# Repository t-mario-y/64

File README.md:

# 64

Splitted, Cherry MX switch, 64 keys, ortholinear mechanical keyboard.

MCU: [Waveshare RP2040-zero](https://www.waveshare.com/wiki/RP2040-Zero)  
Firmware: [KMK firmware](https://github.com/KMKfw/kmk_firmware)

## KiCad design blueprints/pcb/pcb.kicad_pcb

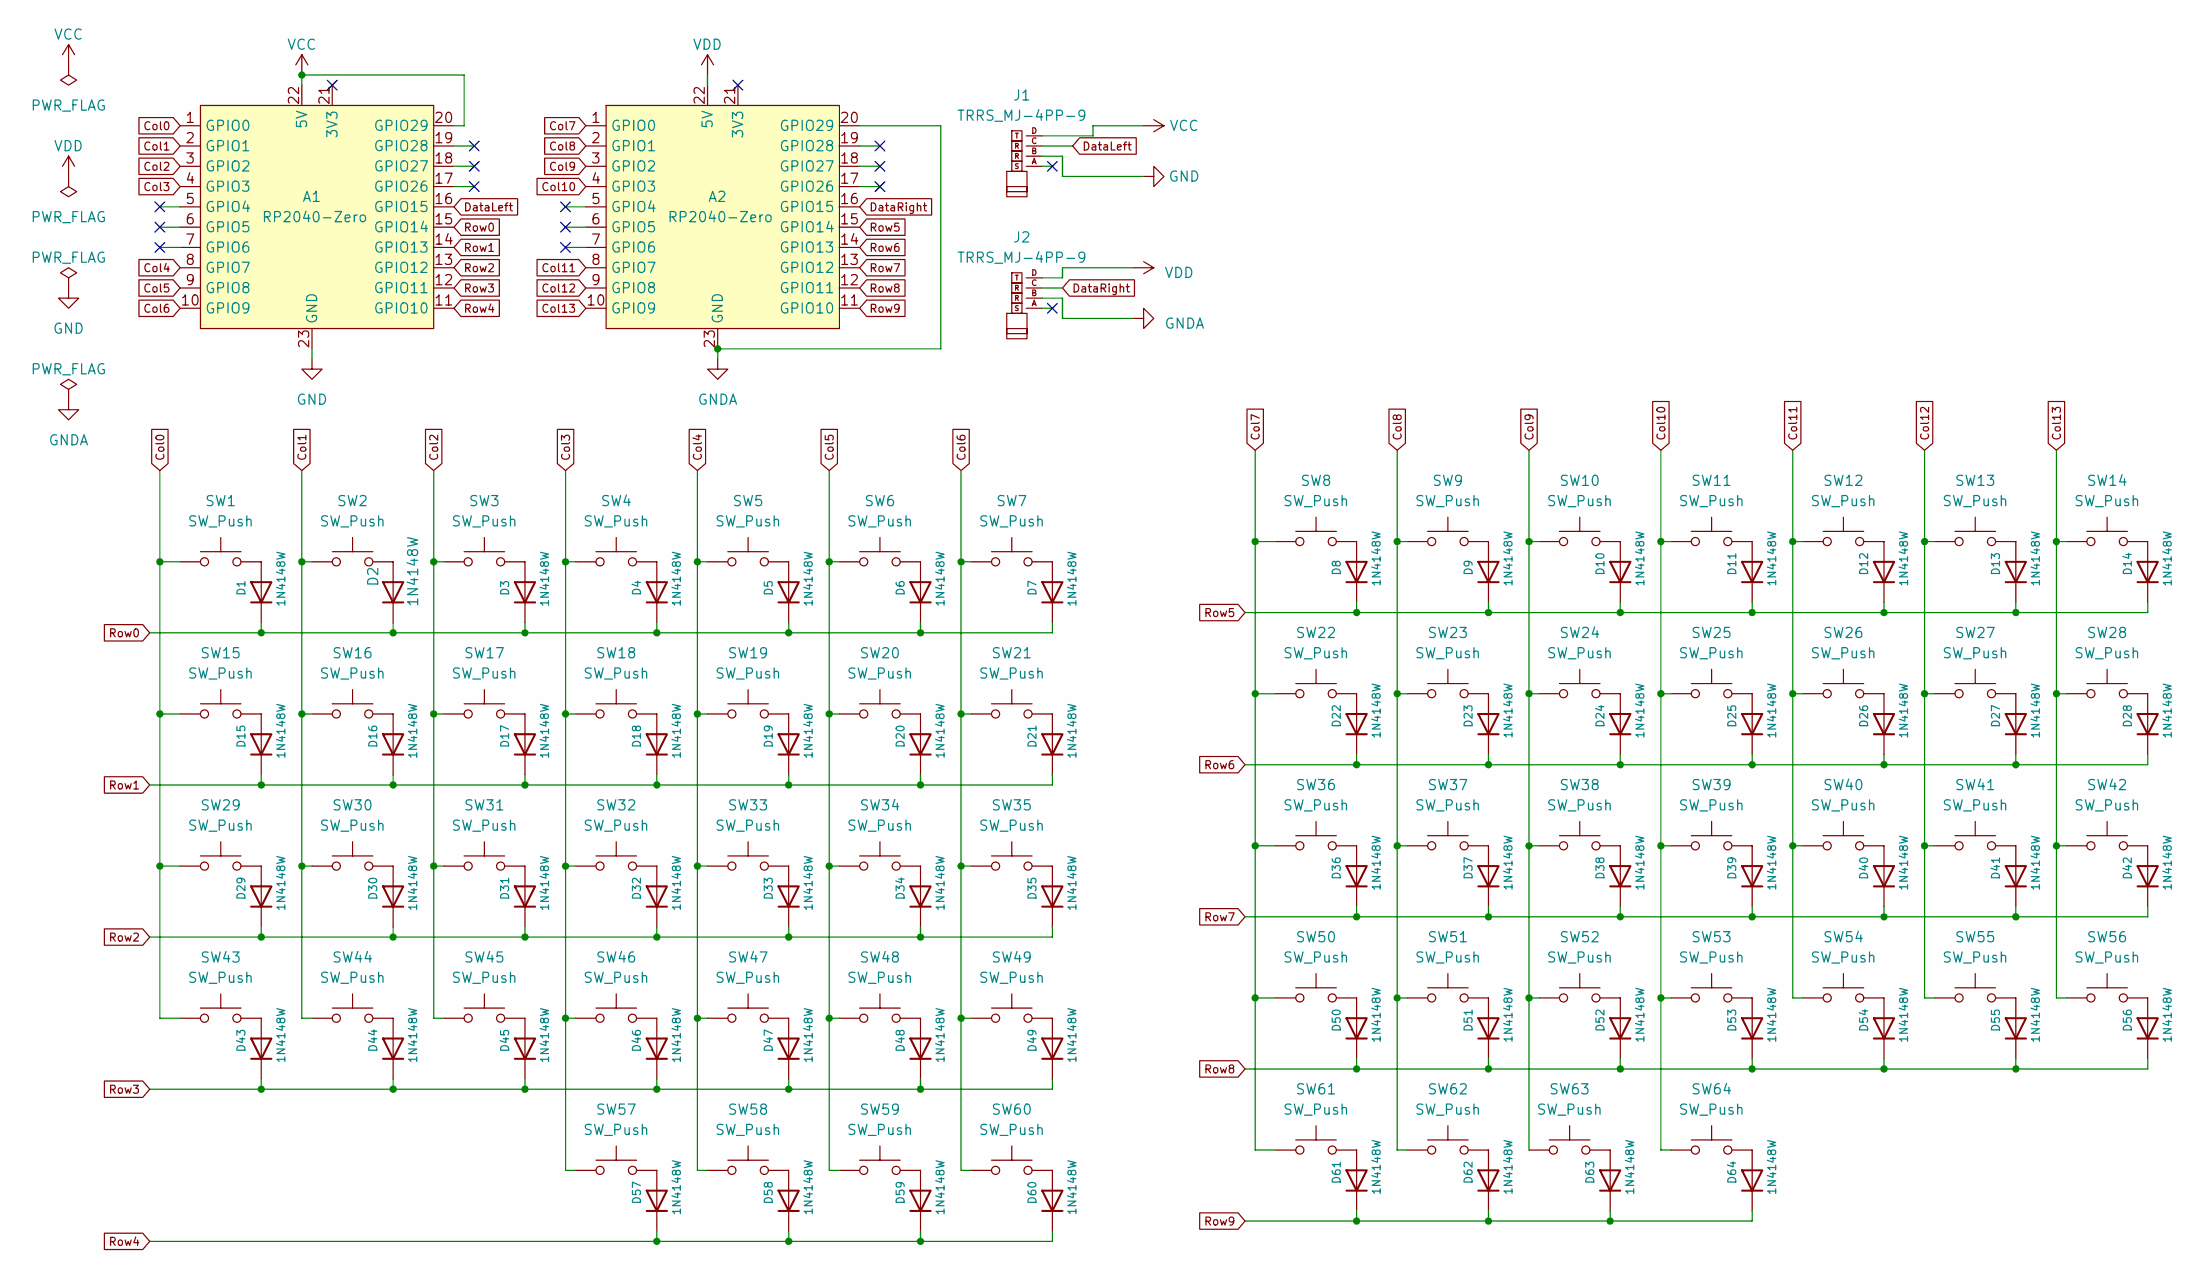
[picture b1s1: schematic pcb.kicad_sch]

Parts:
A1, A2: RP2040-Zero; RP2040-Zero_reversible
D1, D2, D3, D4, D5, D6, D7, D8, D9, D10, D11, D12, D13, D14, D15, D16, D17, D18, D19, D20, D21, D22, D23, D24, D25, D26, D27, D28, D29, D30, D31, D32, D33, D34, D35, D36, D37, D38, D39, D40, D41, D42, D43, D44, D45, D46, D47, D48, D49, D50, D51, D52, D53, D54, D55, D56, D57, D58, D59, D60, D61, D62, D63, D64: 1N4148W; Diode_SMD
J1, J2: TRRS_MJ-4PP-9
SW1, SW2, SW3, SW4, SW5, SW6, SW7, SW8, SW9, SW10, SW11, SW12, SW13, SW14, SW15, SW16, SW17, SW18, SW19, SW20, SW21, SW22, SW23, SW24, SW25, SW26, SW27, SW28, SW29, SW30, SW31, SW32, SW33, SW34, SW35, SW36, SW37, SW38, SW39, SW40, SW41, SW42, SW43, SW44, SW45, SW46, SW47, SW48, SW49, SW50, SW51, SW52, SW53, SW54, SW55, SW56, SW57, SW58, SW59, SW60, SW61, SW62, SW63, SW64: SW_Push; CherryMX_Solder_1u

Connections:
Col0: A1.1 (GPIO0), SW1.1, SW15.1, SW29.1, SW43.1
Col1: A1.2 (GPIO1), SW2.1, SW16.1, SW30.1, SW44.1
Col2: A1.3 (GPIO2), SW3.1, SW17.1, SW31.1, SW45.1
Col3: A1.4 (GPIO3), SW4.1, SW18.1, SW32.1, SW46.1, SW57.1
Col4: A1.8 (GPIO7), SW5.1, SW19.1, SW33.1, SW47.1, SW58.1
Col5: A1.9 (GPIO8), SW6.1, SW20.1, SW34.1, SW48.1, SW59.1
Col6: A1.10 (GPIO9), SW7.1, SW21.1, SW35.1, SW49.1, SW60.1
Col7: A2.1 (GPIO0), SW8.1, SW22.1, SW36.1, SW50.1, SW61.1
Col8: A2.2 (GPIO1), SW9.1, SW23.1, SW37.1, SW51.1, SW62.1
Col9: A2.3 (GPIO2), SW10.1, SW24.1, SW38.1, SW52.1, SW63.1
Col10: A2.4 (GPIO3), SW11.1, SW25.1, SW39.1, SW53.1, SW64.1
Col11: A2.8 (GPIO7), SW12.1, SW26.1, SW40.1, SW54.1
Col12: A2.9 (GPIO8), SW13.1, SW27.1, SW41.1, SW55.1
Col13: A2.10 (GPIO9), SW14.1, SW28.1, SW42.1, SW56.1
DataLeft: A1.16 (GPIO15), J1.C
DataRight: A2.16 (GPIO15), J2.C
GND: A1.23 (GND), J1.B
GNDA: A2.20 (GPIO29), A2.23 (GND), J2.B
unnamed: D1.2 (A), SW1.2
unnamed: D2.2 (A), SW2.2
unnamed: D3.2 (A), SW3.2
unnamed: D4.2 (A), SW4.2
unnamed: D5.2 (A), SW5.2
unnamed: D6.2 (A), SW6.2
unnamed: D7.2 (A), SW7.2
unnamed: D8.2 (A), SW8.2
unnamed: D9.2 (A), SW9.2
unnamed: D10.2 (A), SW10.2
unnamed: D11.2 (A), SW11.2
unnamed: D12.2 (A), SW12.2
unnamed: D13.2 (A), SW13.2
unnamed: D14.2 (A), SW14.2
unnamed: D15.2 (A), SW15.2
unnamed: D16.2 (A), SW16.2
unnamed: D17.2 (A), SW17.2
unnamed: D18.2 (A), SW18.2
unnamed: D19.2 (A), SW19.2
unnamed: D20.2 (A), SW20.2
unnamed: D21.2 (A), SW21.2
unnamed: D22.2 (A), SW22.2
unnamed: D23.2 (A), SW23.2
unnamed: D24.2 (A), SW24.2
unnamed: D25.2 (A), SW25.2
unnamed: D26.2 (A), SW26.2
unnamed: D27.2 (A), SW27.2
unnamed: D28.2 (A), SW28.2
unnamed: D29.2 (A), SW29.2
unnamed: D30.2 (A), SW30.2
unnamed: D31.2 (A), SW31.2
unnamed: D32.2 (A), SW32.2
unnamed: D33.2 (A), SW33.2
unnamed: D34.2 (A), SW34.2
unnamed: D35.2 (A), SW35.2
unnamed: D36.2 (A), SW36.2
unnamed: D37.2 (A), SW37.2
unnamed: D38.2 (A), SW38.2
unnamed: D39.2 (A), SW39.2
unnamed: D40.2 (A), SW40.2
unnamed: D41.2 (A), SW41.2
unnamed: D42.2 (A), SW42.2
unnamed: D43.2 (A), SW43.2
unnamed: D44.2 (A), SW44.2
unnamed: D45.2 (A), SW45.2
unnamed: D46.2 (A), SW46.2
unnamed: D47.2 (A), SW47.2
unnamed: D48.2 (A), SW48.2
unnamed: D49.2 (A), SW49.2
unnamed: D50.2 (A), SW50.2
unnamed: D51.2 (A), SW51.2
unnamed: D52.2 (A), SW52.2
unnamed: D53.2 (A), SW53.2
unnamed: D54.2 (A), SW54.2
unnamed: D55.2 (A), SW55.2
unnamed: D56.2 (A), SW56.2
unnamed: D57.2 (A), SW57.2
unnamed: D58.2 (A), SW58.2
unnamed: D59.2 (A), SW59.2
unnamed: D60.2 (A), SW60.2
unnamed: D61.2 (A), SW61.2
unnamed: D62.2 (A), SW62.2
unnamed: D63.2 (A), SW63.2
unnamed: D64.2 (A), SW64.2
Row0: A1.15 (GPIO14), D1.1 (K), D2.1 (K), D3.1 (K), D4.1 (K), D5.1 (K), D6.1 (K), D7.1 (K)
Row1: A1.14 (GPIO13), D15.1 (K), D16.1 (K), D17.1 (K), D18.1 (K), D19.1 (K), D20.1 (K), D21.1 (K)
Row2: A1.13 (GPIO12), D29.1 (K), D30.1 (K), D31.1 (K), D32.1 (K), D33.1 (K), D34.1 (K), D35.1 (K)
Row3: A1.12 (GPIO11), D43.1 (K), D44.1 (K), D45.1 (K), D46.1 (K), D47.1 (K), D48.1 (K), D49.1 (K)
Row4: A1.11 (GPIO10), D57.1 (K), D58.1 (K), D59.1 (K), D60.1 (K)
Row5: A2.15 (GPIO14), D8.1 (K), D9.1 (K), D10.1 (K), D11.1 (K), D12.1 (K), D13.1 (K), D14.1 (K)
Row6: A2.14 (GPIO13), D22.1 (K), D23.1 (K), D24.1 (K), D25.1 (K), D26.1 (K), D27.1 (K), D28.1 (K)
Row7: A2.13 (GPIO12), D36.1 (K), D37.1 (K), D38.1 (K), D39.1 (K), D40.1 (K), D41.1 (K), D42.1 (K)
Row8: A2.12 (GPIO11), D50.1 (K), D51.1 (K), D52.1 (K), D53.1 (K), D54.1 (K), D55.1 (K), D56.1 (K)
Row9: A2.11 (GPIO10), D61.1 (K), D62.1 (K), D63.1 (K), D64.1 (K)
VCC: A1.20 (GPIO29), A1.22 (5V), J1.D
VDD: A2.22 (5V), J2.D

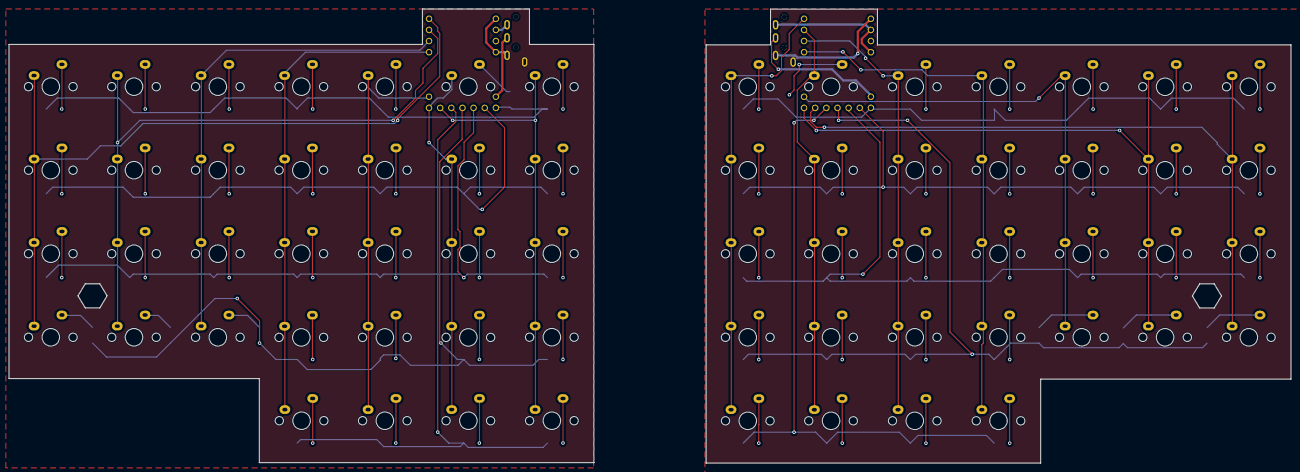
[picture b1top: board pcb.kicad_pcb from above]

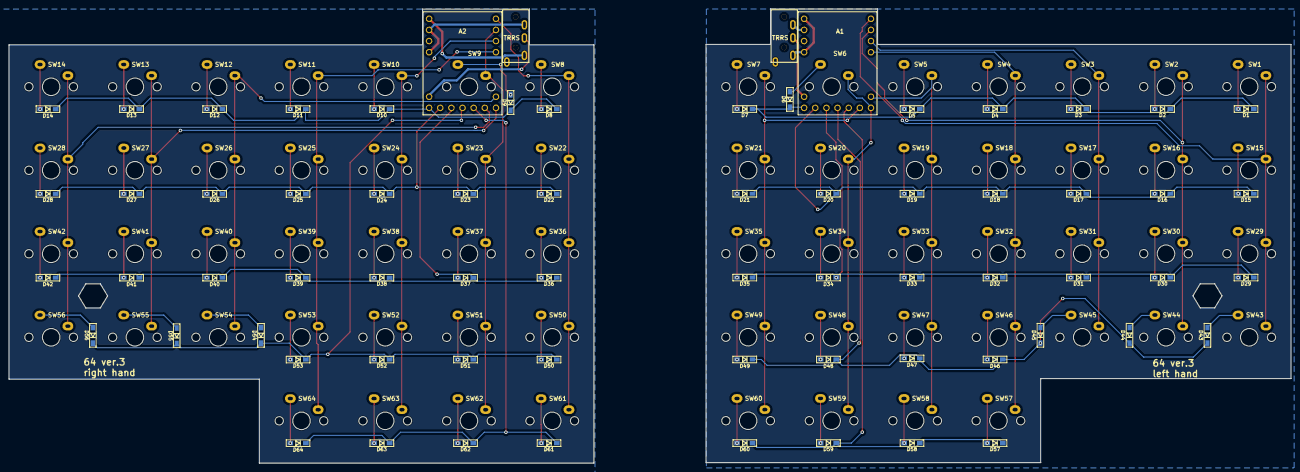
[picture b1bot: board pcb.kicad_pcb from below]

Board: 2 copper layers, 292.4 x 103.6 mm, 132 parts (2 on the bottom side), 94 nets.

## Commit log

2023-02-27 add PCB Schematic
2023-02-27 add symbol library
2023-02-27 update schematic
2023-02-27 fix VCC pin
2023-02-27 add right schematic
2023-02-28 update symbol and footprint library
2023-02-28 use imported symbol for MJ-4PP-9
2023-02-28 import schematic in success
2023-02-28 fix schematic
2023-02-28 edit PCB
2023-03-01 add Raspberry pi pico library
2023-03-01 update KiCad symbol/footprint library
2023-03-01 update PCB, use Raspberry Pi Pico
2023-03-02 チェックエラーが0件になるまでPCB配線した
2023-03-02 reduce silkscreen warnings
2023-03-02 オモテウラを間違えていたので修正
2023-03-04 update libraries
2023-03-05 update PCB
2023-03-05 add 2 switches
2023-03-05 fix PCB Edge.Cuts
2023-03-05 create top and bottom plates
2023-03-05 GNDを塗りつぶし
2023-03-05 print version 0.1
2023-03-05 plot gerber files for v0.1
2023-03-05 rename project to divide PCB and plates
2023-03-05 export gerber for v0.1 again
2023-03-05 modify plate
2023-03-05 divide gerber files for 4 kinds plates
2023-03-05 Raspberry Pi Picoの箇所に穴をあける
2023-03-05 modify PCB and plates
2023-03-05 publish v0.1
2023-03-06 update backup
2023-03-06 update v0.1 gerber
2023-03-11 export step file
2023-03-12 update prl
2023-03-12 add User.Drawings to plate
2023-03-12 narrow left PCB
2023-03-12 narrow right PCB
2023-03-13 print 'ver.2' on plates
2023-03-14 untrack backup files
2023-03-14 modify PCB
2023-03-14 change active layer
2023-03-14 export STEP
2023-03-14 rename
2023-03-15 rename and modify v0.1 files
2023-03-15 add step files for ver2
2023-03-16 print to PDF
2023-03-19 add example
2023-03-19 add mock keymap.rb
2023-03-19 improve example to 4 keys
2023-03-19 export ver.2 gerber files
2023-03-25 enable split keyboard in example
2023-03-25 enable 3 layers in example
2023-03-25 add real keymap.rb
2023-03-25 adjust matrix
2023-03-26 fix keycode typo
2023-03-26 workaround: reverse right hand matrix
2023-03-27 fix keymap
2023-03-28 move schema PDF to dist
2023-04-02 version3
2023-04-02 add gerbers
2023-04-02 add schema
2023-04-02 export models
2023-04-04 update example keymap
2023-04-04 modify for RP2040-zero
2023-04-07 rename dir
2023-04-08 add KMK firmware code
2023-04-08 quit using PRK firmware
2023-04-08 add version memo
2023-04-08 move USB type-C module
2023-04-08 edit KiCad libraries
2023-04-08 add README.md
2023-04-08 modify displaying photo size
2023-04-09 rename variable
2023-04-09 add HoldTap
2023-04-12 add keyboard photo
2023-04-12 update keyboard photo
2023-04-15 export top plate step file from KiCad
2023-04-15 export step & stl files
2023-04-15 export gerber files
2023-04-15 left/right case step & stl files
2023-04-16 remove old versions build
2023-04-16 update silk print text
2023-04-16 remove unused referring
2023-04-16 rename plates project
2023-04-16 export top plate step file
2023-04-16 rename PCB kicad project
2023-04-16 fix 11111 to 64
2023-04-16 plot gerber files
2023-04-16 fix silk print
2023-04-16 export PCB step file
2023-04-16 rename and export models again
2023-04-16 Create LICENSE
